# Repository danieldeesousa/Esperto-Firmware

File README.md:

# Esperto-Labs
Esperto Watch firmware and hardware

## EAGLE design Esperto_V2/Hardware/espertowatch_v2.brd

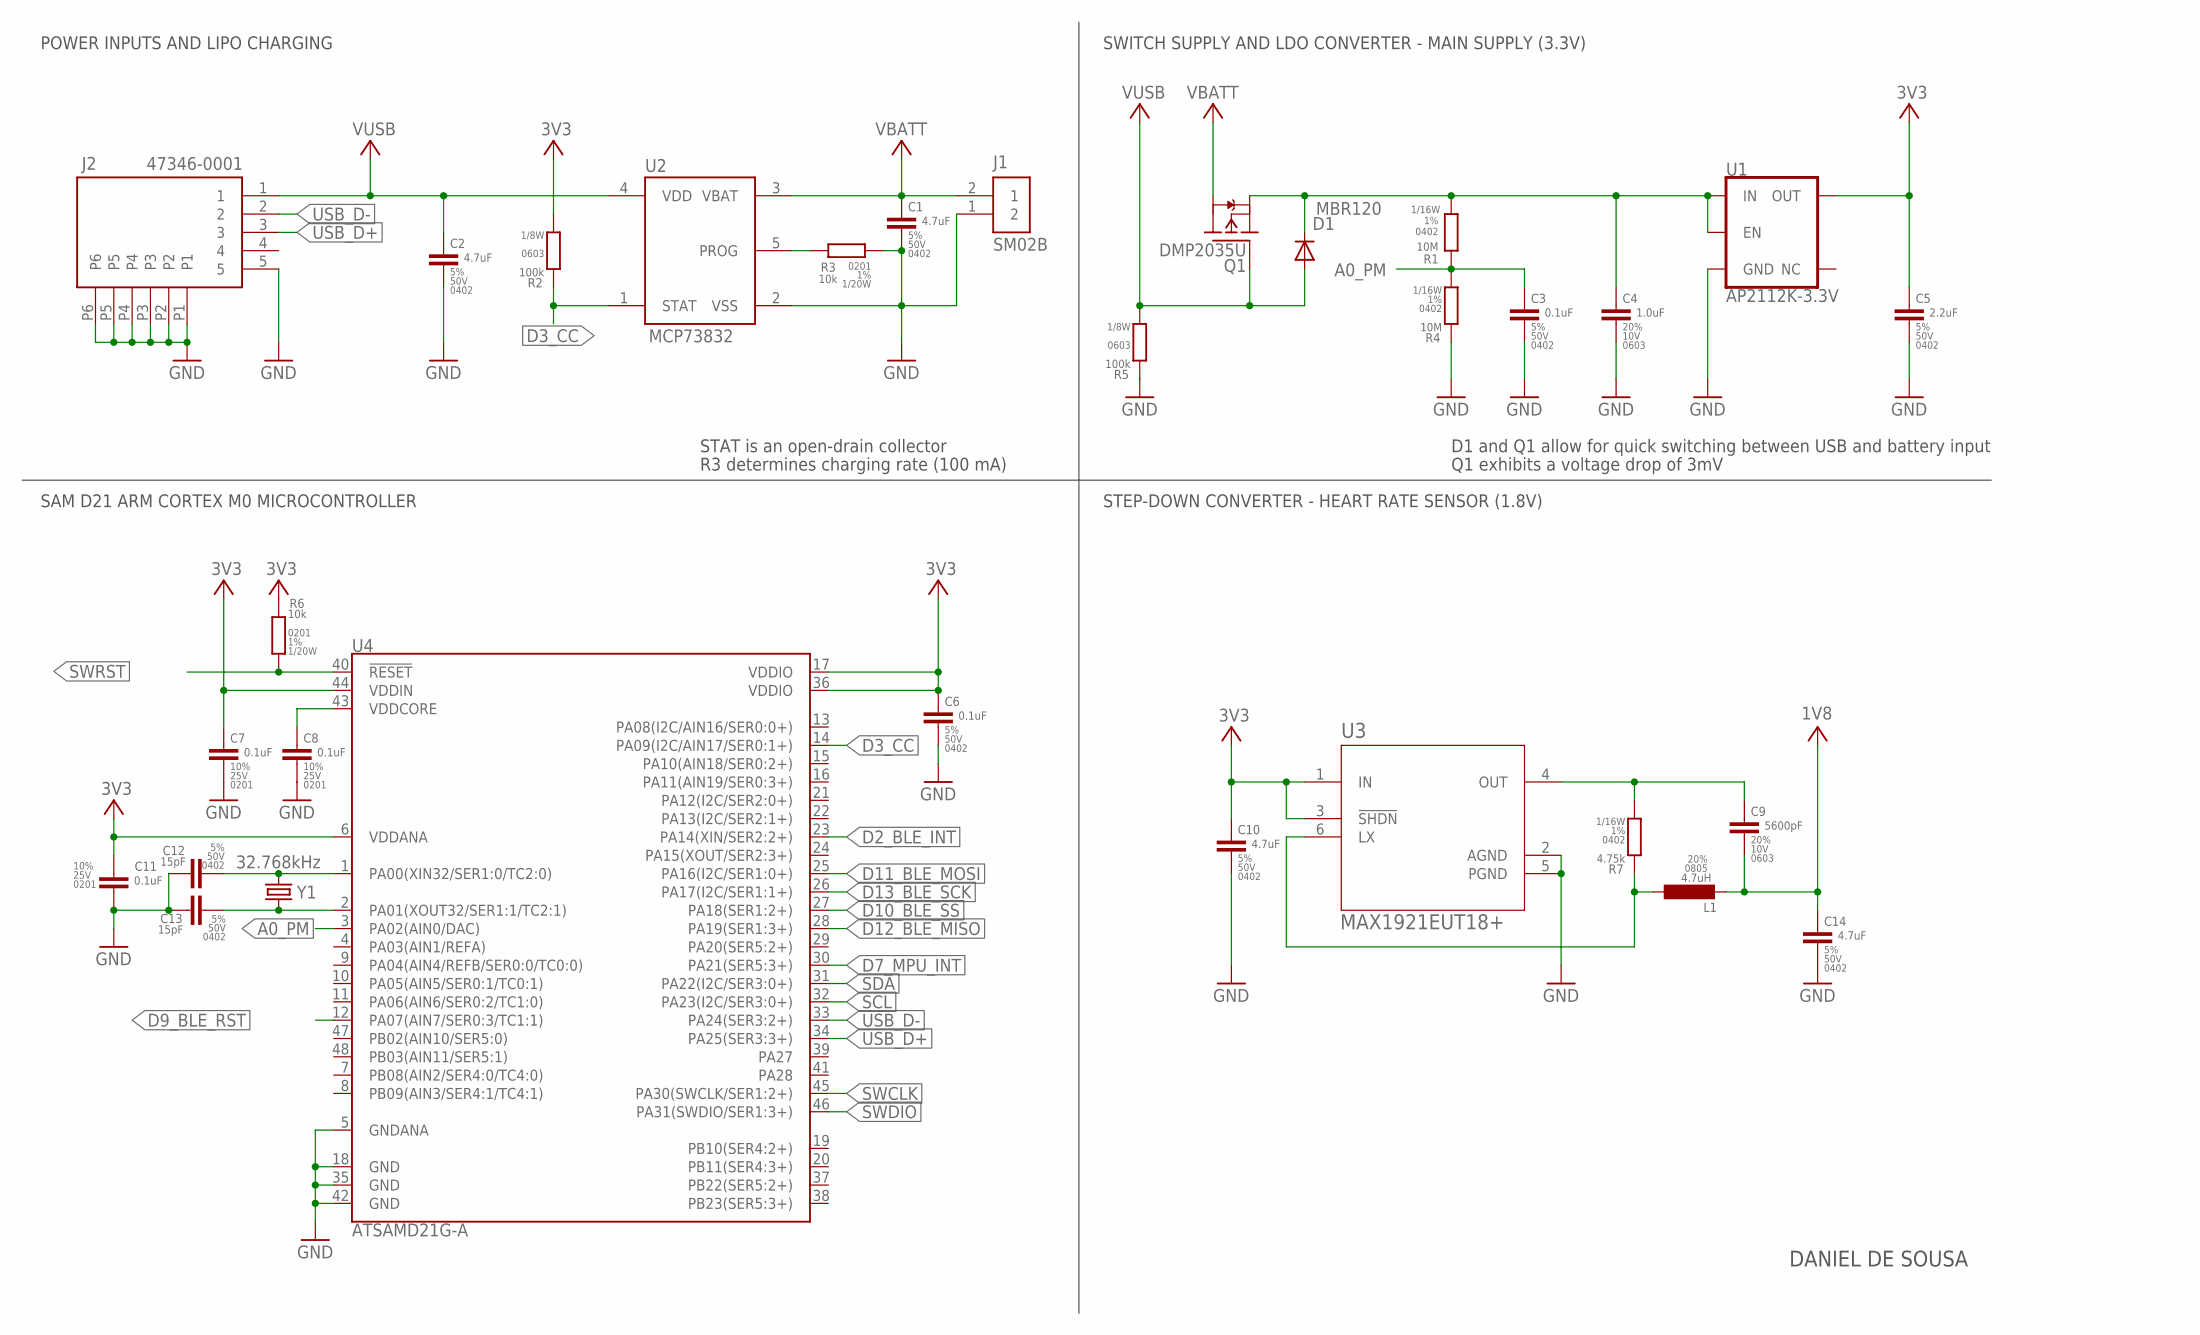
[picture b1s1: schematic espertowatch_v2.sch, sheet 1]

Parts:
C1, C2, C10, C14: 4.7uF; C0402_MURATA_GRM15-GJM15
C3, C6: 0.1uF; C0402_MURATA_GRM15-GJM15
C4: 1.0uF; C0603_MURATA_GRM18
C5: 2.2uF; C0402_MURATA_GRM15-GJM15
C7, C8, C11: 0.1uF; C0201_MURATA_GRM03
C9: 5600pF; C0603_MURATA_GRM18
C12, C13: 15pF; C0402_MURATA_GRM15-GJM15
D1: MBR120; SOD-123FL
J1: SM02B; JST_SH_2X1
J2: 47346-0001; MICRO_USB
L1: 4.7uH; L0805_TDK_MLZ
Q1: DMP2035U; SOT23
R1, R4: 10M; R0402_VISHAY_CRCW0402
R2, R5: 100k; R0603_VISHAY_MCT0603
R3, R6: 10k; R0201_VISHAY_CRCW0201
R7: 4.75k; R0402_VISHAY_CRCW0402
U1: AP2112K-3.3V; SOT23-5
U2: MCP73832; SOT-23
U3: MAX1921EUT18+; 21-0058I
U4: ATSAMD21G-A; TQFP-48
Y1: 32.768kHz; CRYSTAL-SMD-3.2X1.5MM

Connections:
1V8: C9.2, C14.1, L1.P$2 (2); also elsewhere on the board
3V3: C5.1, C6.1, C7.1, C10.1, C11.1, R2.2, R6.1, U1.5 (OUT), U3.1 (IN), U3.3 (!SHDN), U4.6 (VDDANA), U4.17 (VDDIO), U4.36 (VDDIO), U4.44 (VDDIN); also elsewhere on the board
A0_PM: C3.1, R1.1, R4.2, U4.3 (PA02(AIN0/DAC))
D2_BLE_INT: U4.23 (PA14(XIN/SER2:2+)); also elsewhere on the board
D3_CC: R2.1, U2.1 (STAT), U4.14 (PA09(I2C/AIN17/SER0:1+))
D7_MPU_INT: U4.30 (PA21(SER5:3+)); also elsewhere on the board
D9_BLE_RST: U4.12 (PA07(AIN7/SER0:3/TC1:1)); also elsewhere on the board
D10_BLE_SS: U4.27 (PA18(SER1:2+)); also elsewhere on the board
D11_BLE_MOSI: U4.25 (PA16(I2C/SER1:0+)); also elsewhere on the board
D12_BLE_MISO: U4.28 (PA19(SER1:3+)); also elsewhere on the board
D13_BLE_SCK: U4.26 (PA17(I2C/SER1:1+)); also elsewhere on the board
GND: C1.2, C2.2, C3.2, C4.2, C5.2, C6.2, C7.2, C8.2, C10.2, C11.2, C12.1, C13.1, C14.2, J1.1 (2), J2.5, J2.P1, J2.P2, J2.P3, J2.P4, J2.P5, J2.P6, R3.2, R4.1, R5.1, U1.2 (GND), U2.2 (VSS), U3.2 (AGND), U3.5 (PGND), U4.5 (GNDANA), U4.18 (GND), U4.35 (GND), U4.42 (GND); also elsewhere on the board
unnamed: C4.1, D1.C, Q1.E (S), R1.2, U1.1 (IN), U1.3 (EN)
unnamed: R3.1, U2.5 (PROG)
unnamed: C8.1, U4.43 (VDDCORE)
unnamed: C12.2, U4.1 (PA00(XIN32/SER1:0/TC2:0)), Y1.P$2 (2)
unnamed: C13.2, U4.2 (PA01(XOUT32/SER1:1/TC2:1)), Y1.P$1 (1)
unnamed: L1.P$1 (1), R7.1, U3.6 (LX)
unnamed: C9.1, R7.2, U3.4 (OUT)
SCL: U4.32 (PA23(I2C/SER3:0+)); also elsewhere on the board
SDA: U4.31 (PA22(I2C/SER3:0+)); also elsewhere on the board
SWCLK: U4.45 (PA30(SWCLK/SER1:2+)); also elsewhere on the board
SWDIO: U4.46 (PA31(SWDIO/SER1:3+)); also elsewhere on the board
SWRST: R6.2, U4.40 (!RESET!); also elsewhere on the board
USB_D+: J2.3, U4.34 (PA25(SER3:3+))
USB_D-: J2.2, U4.33 (PA24(SER3:2+))
VBATT: C1.1, J1.2 (1), Q1.C (D), U2.3 (VBAT)
VUSB: C2.1, D1.A, J2.1, Q1.B (G), R5.2, U2.4 (VDD)

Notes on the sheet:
SAM D21 ARM CORTEX M0 MICROCONTROLLER
STEP-DOWN CONVERTER - HEART RATE SENSOR (1.8V)
POWER INPUTS AND LIPO CHARGING
SWITCH SUPPLY AND LDO CONVERTER - MAIN SUPPLY (3.3V)
STAT is an open-drain collector
R3 determines charging rate (100 mA)
D1 and Q1 allow for quick switching between USB and battery input
DANIEL DE SOUSA
Q1 exhibits a voltage drop of 3mV

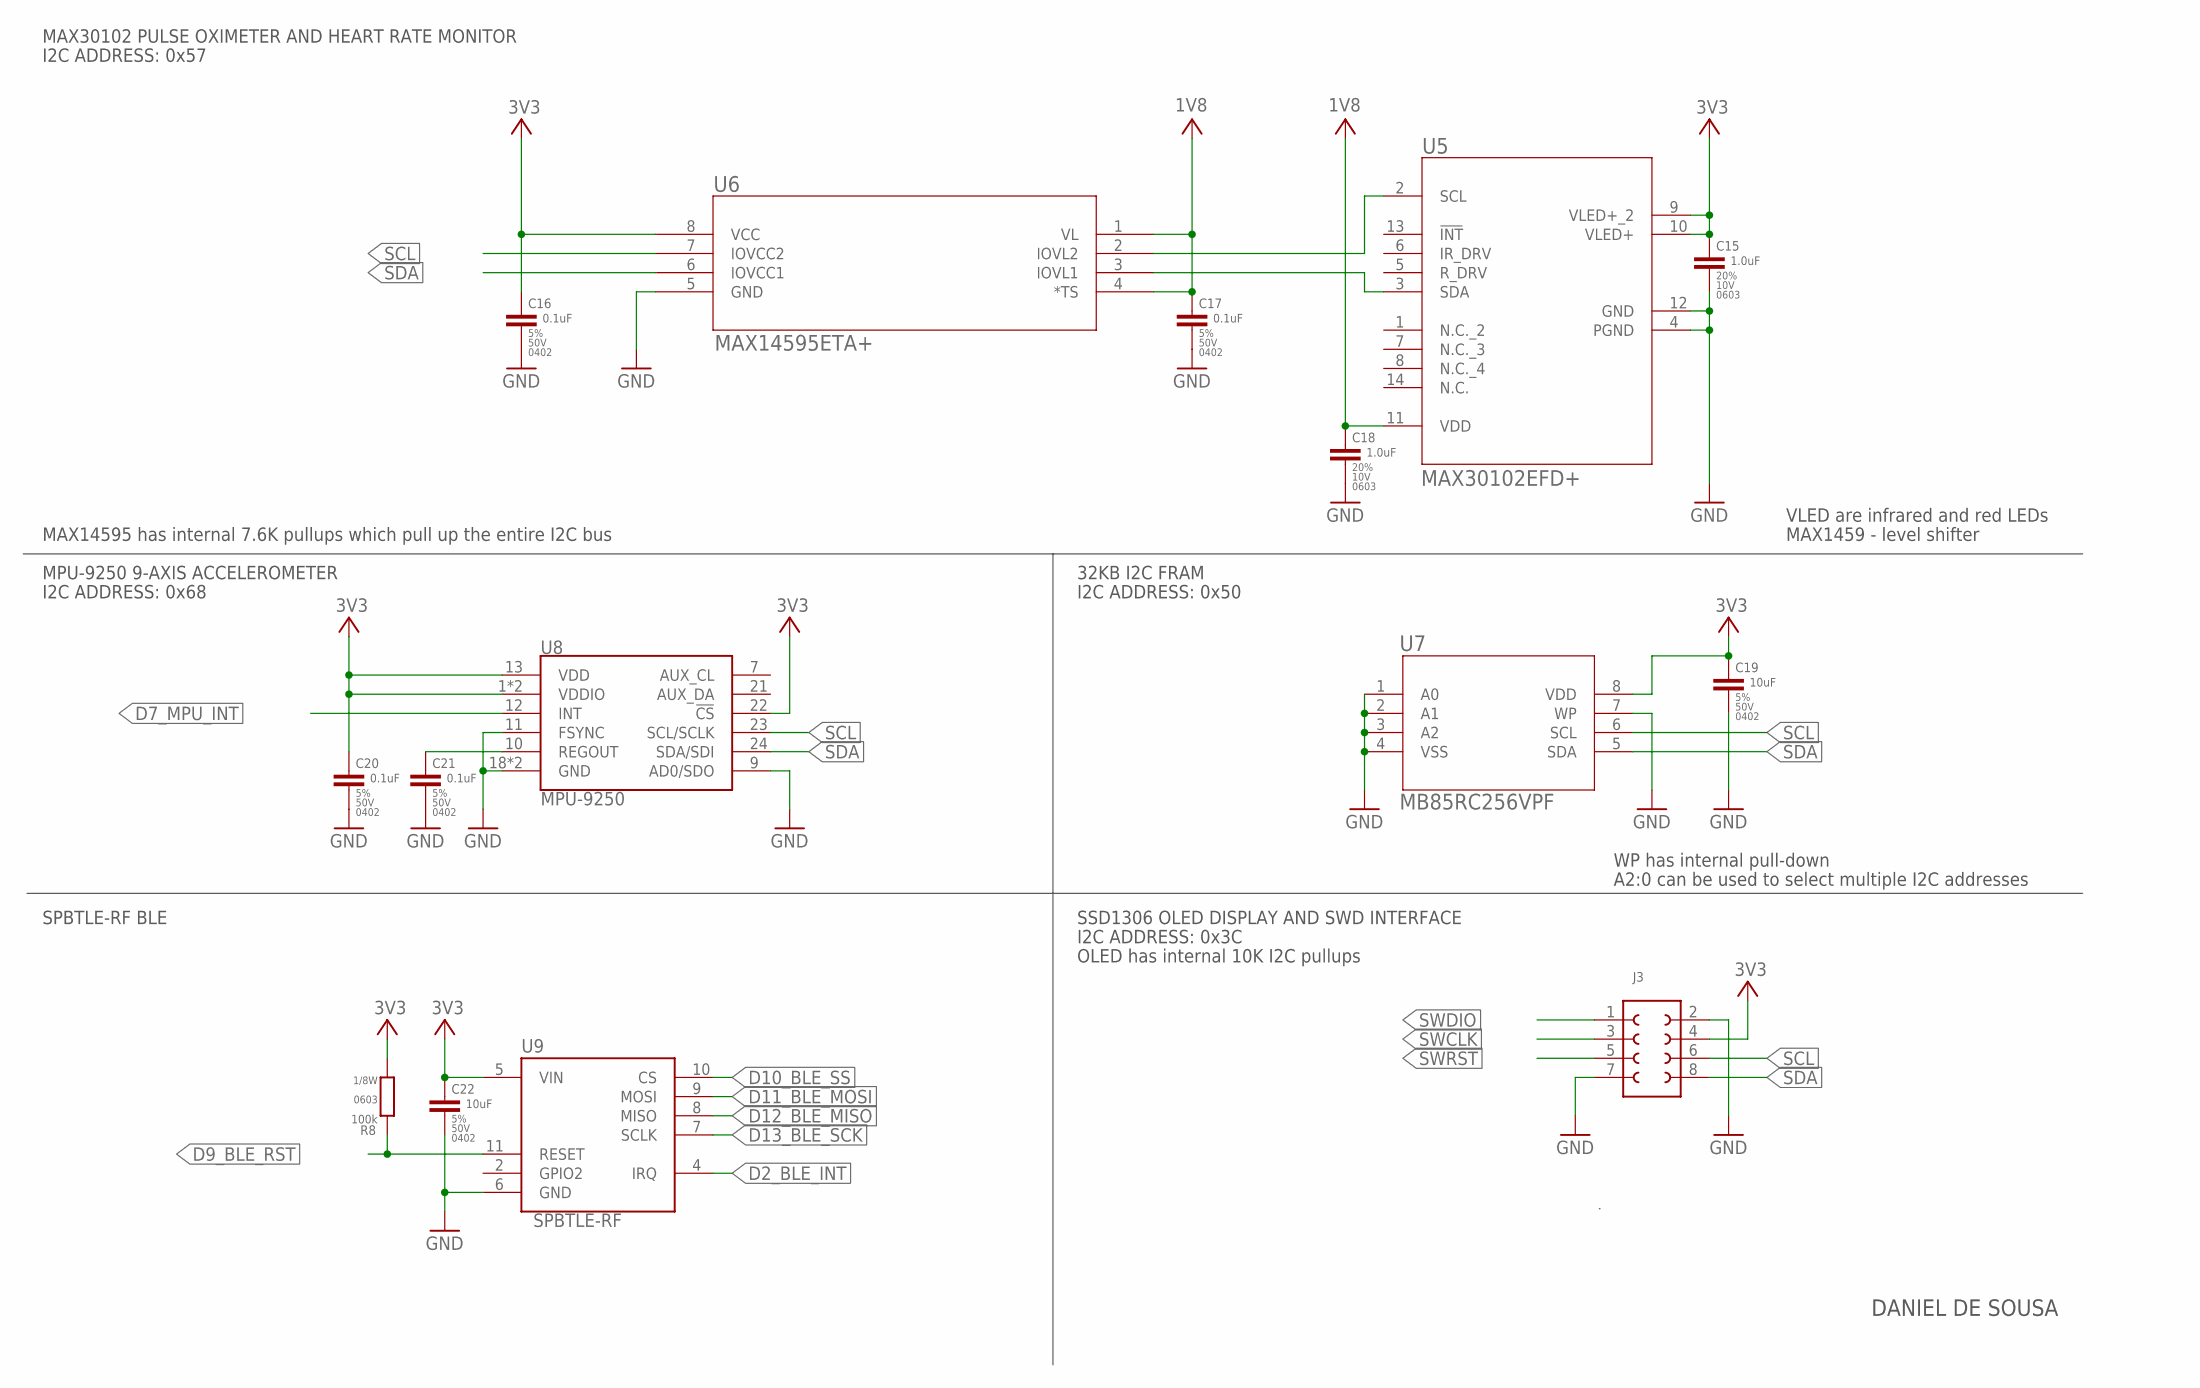
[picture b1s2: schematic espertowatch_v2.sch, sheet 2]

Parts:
C15, C18: 1.0uF; C0603_MURATA_GRM18
C16, C17, C20, C21: 0.1uF; C0402_MURATA_GRM15-GJM15
C19, C22: 10uF; C0402_MURATA_GRM15-GJM15
J3: 610X08243021
R8: 100k; R0603_VISHAY_MCT0603
U5: MAX30102EFD+; 21-0880B-M
U6: MAX14595ETA+; 21-0487A
U7: MB85RC256VPF; FPT-8P-M02
U8: MPU-9250; QFN24-3X3
U9: SPBTLE-RF

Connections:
1V8: C17.1, C18.1, U5.11 (VDD), U6.1 (VL), U6.4 (*TS); also elsewhere on the board
3V3: C15.1, C16.1, C19.1, C20.1, C22.1, J3.4 (7), R8.2, U5.9 (VLED+_2), U5.10 (VLED+), U6.8 (VCC), U7.8 (VDD), U8.1 (VDDIO), U8.8 (VDDIO), U8.13 (VDD), U8.22 (!CS), U9.5 (VIN); also elsewhere on the board
D2_BLE_INT: U9.4 (IRQ); also elsewhere on the board
D7_MPU_INT: U8.12 (INT); also elsewhere on the board
D9_BLE_RST: R8.1, U9.11 (RESET); also elsewhere on the board
D10_BLE_SS: U9.10 (CS); also elsewhere on the board
D11_BLE_MOSI: U9.9 (MOSI); also elsewhere on the board
D12_BLE_MISO: U9.8 (MISO); also elsewhere on the board
D13_BLE_SCK: U9.7 (SCLK); also elsewhere on the board
GND: C15.2, C16.2, C17.2, C18.2, C19.2, C20.2, C21.2, C22.2, J3.2 (8), J3.7 (4), U5.4 (PGND), U5.12 (GND), U6.5 (GND), U7.1 (A0), U7.2 (A1), U7.3 (A2), U7.4 (VSS), U7.7 (WP), U8.9 (AD0/SDO), U8.11 (FSYNC), U8.18 (GND), U8.20 (GND), U9.6 (GND); also elsewhere on the board
unnamed: C21.1, U8.10 (REGOUT)
unnamed: U5.2 (SCL), U6.2 (IOVL2)
unnamed: U5.3 (SDA), U6.3 (IOVL1)
SCL: J3.6, U6.7 (IOVCC2), U7.6 (SCL), U8.23 (SCL/SCLK); also elsewhere on the board
SDA: J3.8 (5), U6.6 (IOVCC1), U7.5 (SDA), U8.24 (SDA/SDI); also elsewhere on the board
SWCLK: J3.3 (2); also elsewhere on the board
SWDIO: J3.1; also elsewhere on the board
SWRST: J3.5 (3); also elsewhere on the board

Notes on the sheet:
32KB I2C FRAM
SPBTLE-RF BLE
MPU-9250 9-AXIS ACCELEROMETER
MAX30102 PULSE OXIMETER AND HEART RATE MONITOR
SSD1306 OLED DISPLAY AND SWD INTERFACE
VLED are infrared and red LEDs
MAX1459 - level shifter
WP has internal pull-down
A2:0 can be used to select multiple I2C addresses
DANIEL DE SOUSA
MAX14595 has internal 7.6K pullups which pull up the entire I2C bus
OLED has internal 10K I2C pullups
I2C ADDRESS: 0x3C
I2C ADDRESS: 0x50
I2C ADDRESS: 0x68
I2C ADDRESS: 0x57

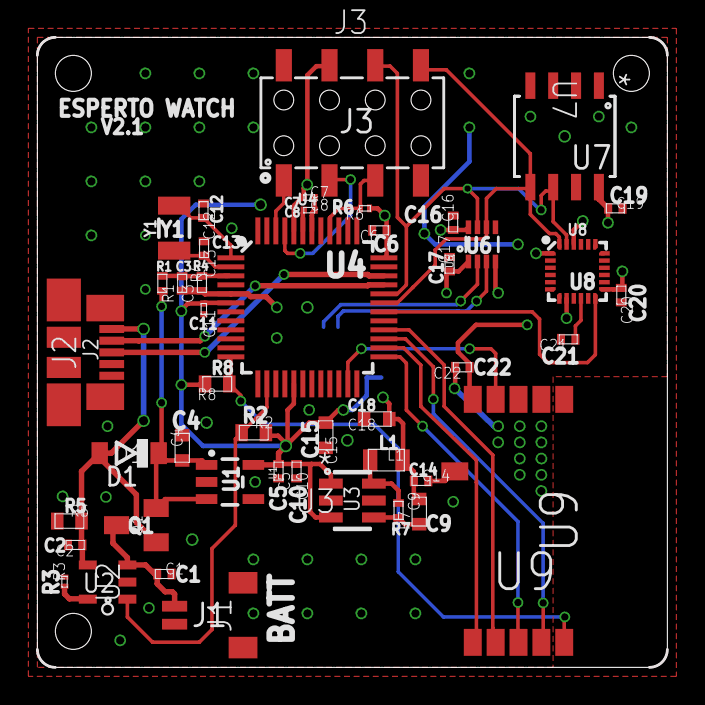
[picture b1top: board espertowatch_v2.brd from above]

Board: 2 copper layers, 35.0 x 35.0 mm, 46 parts (1 on the bottom side), 31 nets.

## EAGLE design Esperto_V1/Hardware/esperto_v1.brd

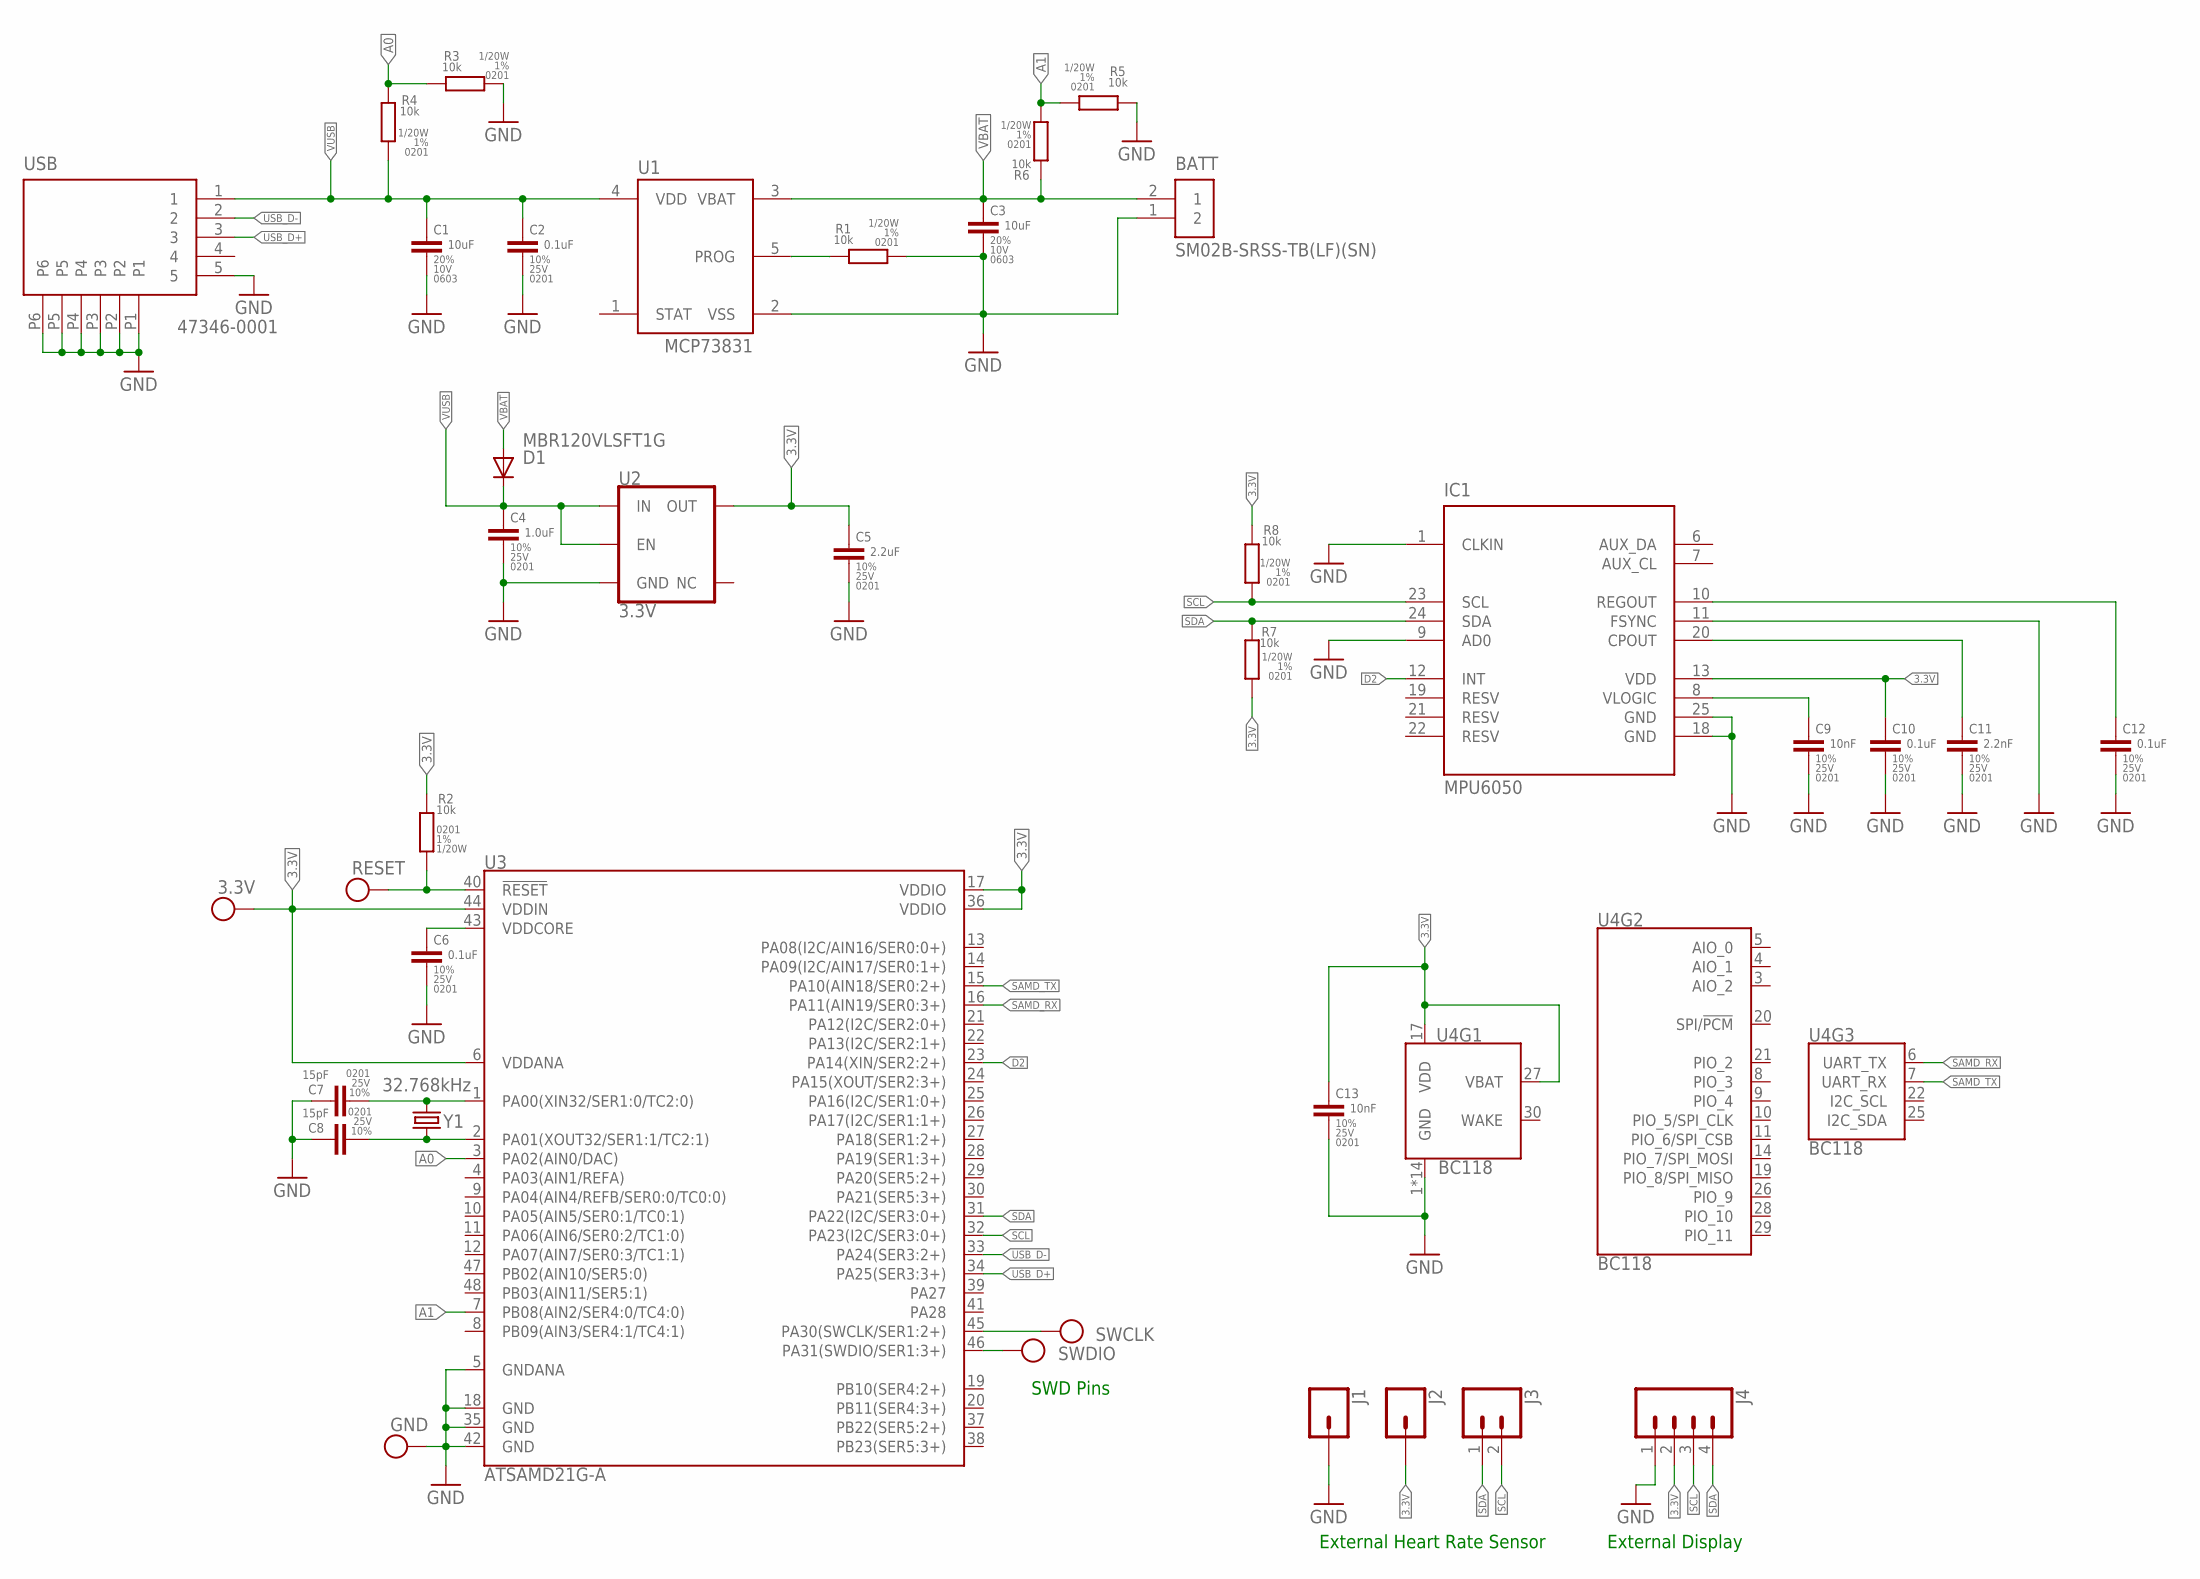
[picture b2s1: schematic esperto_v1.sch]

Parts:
3.3V: PIN_1X.05"1; 1X.05"
BATT: SM02B-SRSS-TB(LF)(SN); JST_SH_2X1
C1, C3: 10uF; C0603_MURATA_GRM18
C2, C6, C10, C12: 0.1uF; C0201_MURATA_GRM03
C4: 1.0uF; C0201_MURATA_GRM03
C5: 2.2uF; C0201_MURATA_GRM03
C7, C8: 15pF; C0201_MURATA_GRM03
C9, C13: 10nF; C0201_MURATA_GRM03
C11: 2.2nF; C0201_MURATA_GRM03
D1: MBR120VLSFT1G; SOD-123FL
GND: PIN_1X.05"1; 1X.05"
IC1: MPU6050; QFN50P400X400X95-25T265X275N
J1, J2: CONN_01; 1X01
J3: CONN_02; 1X02
J4: CONN_04; 1X04
R1, R2, R3, R4, R5, R6, R7, R8: 10k; R0201_VISHAY_CRCW0201
RESET: PIN_1X.05"1; 1X.05"
SWCLK: PIN_1X.05"1; 1X.05"
SWDIO: PIN_1X.05"1; 1X.05"
U1: MCP73831; SOT-23
U2: 3.3V; SOT23-5
U3: ATSAMD21G-A; TQFP-48
U4: BC118
USB: 47346-0001; MICRO_USB
Y1: 32.768kHz; CRYSTAL-SMD-3.2X1.5MM

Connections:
3.3V: 3.3V.1, C5.1, C10.1, C13.1, IC1.13 (VDD), J2.1, J4.2, R2.1, R7.2, R8.1, U2.5 (OUT), U3.6 (VDDANA), U3.17 (VDDIO), U3.36 (VDDIO), U3.44 (VDDIN), U4.17 (VDD), U4.27 (VBAT)
A0: R3.1, R4.1, U3.3 (PA02(AIN0/DAC))
A1: R5.2, R6.2, U3.7 (PB08(AIN2/SER4:0/TC4:0))
D2: IC1.12 (INT), U3.23 (PA14(XIN/SER2:2+))
GND: BATT.1 (2), C1.2, C2.2, C3.2, C4.2, C5.2, C6.2, C7.1, C8.1, C9.2, C10.2, C11.2, C12.2, C13.2, GND.1, IC1.1 (CLKIN), IC1.9 (AD0), IC1.11 (FSYNC), IC1.18 (GND), IC1.25 (GND), J1.1, J4.1, R1.2, R3.2, R5.1, U1.2 (VSS), U2.2 (GND), U3.5 (GNDANA), U3.18 (GND), U3.35 (GND), U3.42 (GND), U4.1 (GND), U4.2 (GND), U4.12 (GND), U4.13 (GND), U4.15 (GND), U4.16 (GND), U4.18 (GND), U4.23 (GND), U4.24 (GND), U4.31 (GND), U4.32 (GND), U4.33 (GND), U4.34 (GND), U4.35 (GND), USB.5, USB.P1, USB.P2, USB.P3, USB.P4, USB.P5, USB.P6
unnamed: R1.1, U1.5 (PROG)
unnamed: R2.2, RESET.1, U3.40 (!RESET!)
unnamed: C6.1, U3.43 (VDDCORE)
unnamed: C7.2, U3.1 (PA00(XIN32/SER1:0/TC2:0)), Y1.P$1 (1)
unnamed: C8.2, U3.2 (PA01(XOUT32/SER1:1/TC2:1)), Y1.P$2 (2)
unnamed: SWCLK.1, U3.45 (PA30(SWCLK/SER1:2+))
unnamed: SWDIO.1, U3.46 (PA31(SWDIO/SER1:3+))
unnamed: C9.1, IC1.8 (VLOGIC)
unnamed: C11.1, IC1.20 (CPOUT)
unnamed: C12.1, IC1.10 (REGOUT)
SAMD_RX: U3.16 (PA11(AIN19/SER0:3+)), U4.6 (UART_TX)
SAMD_TX: U3.15 (PA10(AIN18/SER0:2+)), U4.7 (UART_RX)
SCL: IC1.23 (SCL), J3.2, J4.3, R8.2, U3.32 (PA23(I2C/SER3:0+))
SDA: IC1.24 (SDA), J3.1, J4.4, R7.1, U3.31 (PA22(I2C/SER3:0+))
USB_D+: U3.34 (PA25(SER3:3+)), USB.3
USB_D-: U3.33 (PA24(SER3:2+)), USB.2
VBAT: BATT.2 (1), C3.1, D1.A, R6.1, U1.3 (VBAT)
VUSB: C1.1, C2.1, C4.1, D1.C, R4.2, U1.4 (VDD), U2.1 (IN), U2.3 (EN), USB.1

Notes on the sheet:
External Heart Rate Sensor
External Display
SWD Pins

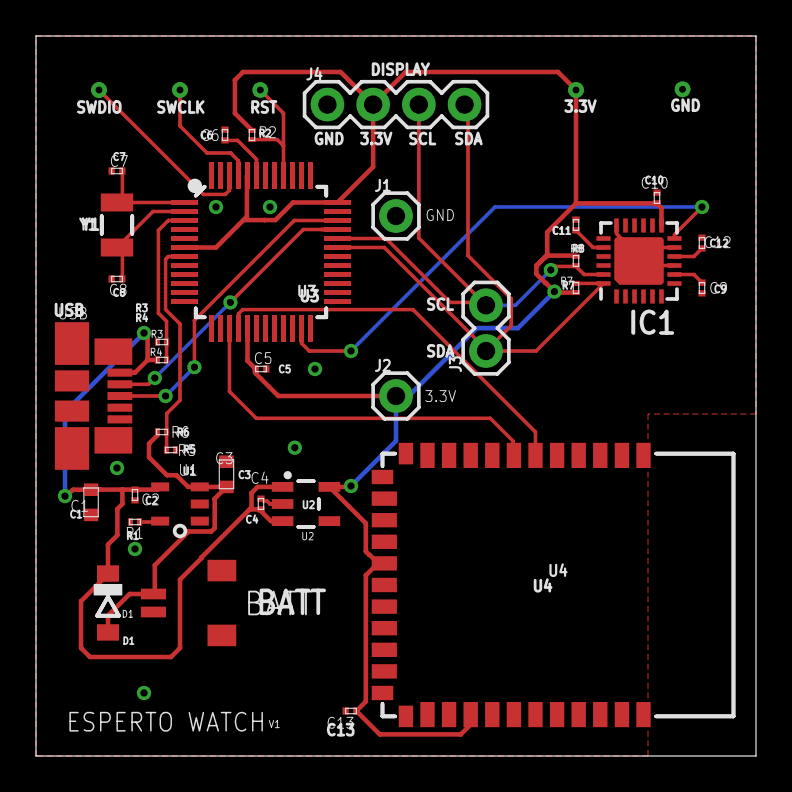
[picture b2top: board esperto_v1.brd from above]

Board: 2 copper layers, 40.0 x 40.0 mm, 39 parts (0 on the bottom side), 23 nets.

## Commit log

2018-02-26 :confetti_ball: Added .gitattributes & .gitignore files
2018-02-26 Removed everything but firmware
2018-02-27 Comments
2018-06-21 Added Esperto Version 2 and hardware files
2018-06-21 Add main app v2
2018-06-24 Added new hardware and EAGLE libraries
2018-07-09 BLE support for APP - bug fixes
2018-07-13 Added DMP step rate detection
2018-07-17 Refactored FRAM and RTC - added legacy support
2018-07-18 Refactored timer library
2018-07-24 Refactored BLE
2018-07-24 Read Me
2018-07-25 Refactored Libraries
2018-07-26 Refactored MAX30102 and MPU9250
2018-07-27 Added Esperto library support
2018-07-30 Fully refactored firmware
2018-08-09 Added power management functionality
2018-08-09 Rebase
2018-08-14 Added SpO2
2018-08-14 Added SpO2 comments
2018-08-14 Example code
2018-08-16 Timer updates and refactoring
2018-08-18 Version 2.1.0. Fine tuned step detection, fixed bugs, wrist movement detection
2018-08-18 Typos
2018-08-21 Fixed step count
2018-08-21 Definition changes
2018-08-23 Updated accel Z thresholds
2018-08-24 Format
2018-08-28 SpO2 refactoring
2018-08-29 Added SpO2 explentation
2018-08-29 Added documentation
2018-08-31 Removed I2C pullups
2018-09-07 Modified power management state machine
2018-09-11 USB management
2018-09-18 Add shutdown voltage hysteresis and new logo
2018-09-19 Reverse FRAM burst
2018-09-20 Burst transfer footers
2018-09-21 NYC demo
2019-04-25 Esperto V3 Hardware
2019-04-25 Firmware folder
2019-09-11 DFM issues

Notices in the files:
parts and their libraries:
SparkFun-IC-Power: Licensing: Creative Commons ShareAlike 4.0 International - https://creativecommons.org/licenses/by-sa/4.0
Board-to-Board: Copyright: Würth Elektronik
